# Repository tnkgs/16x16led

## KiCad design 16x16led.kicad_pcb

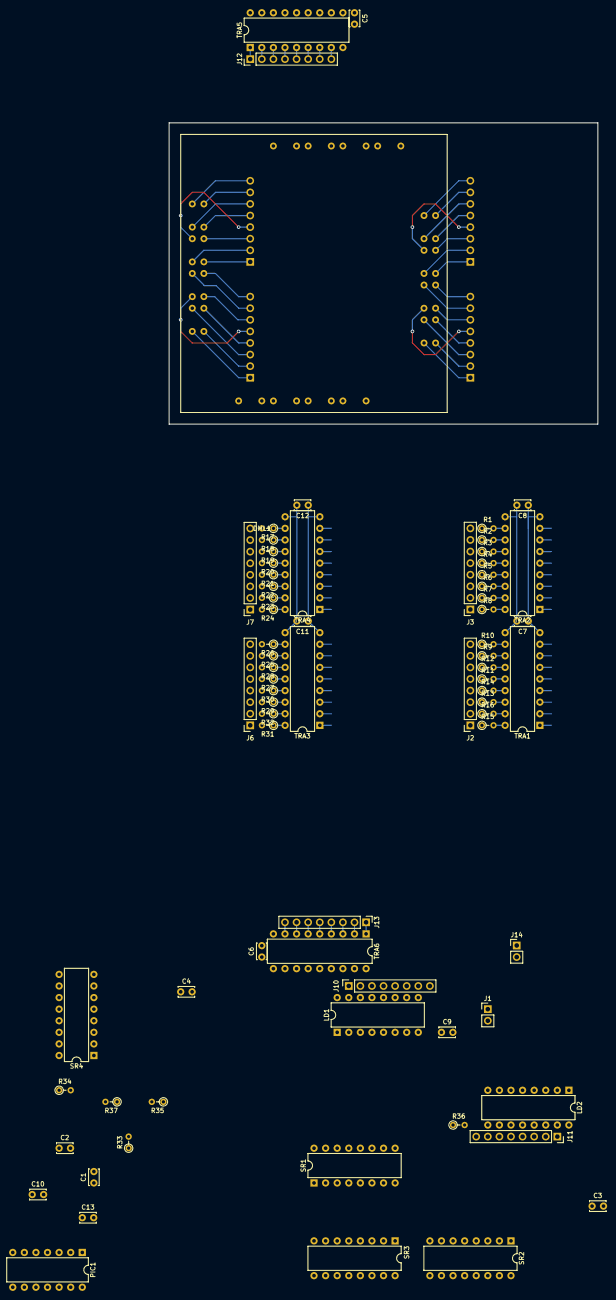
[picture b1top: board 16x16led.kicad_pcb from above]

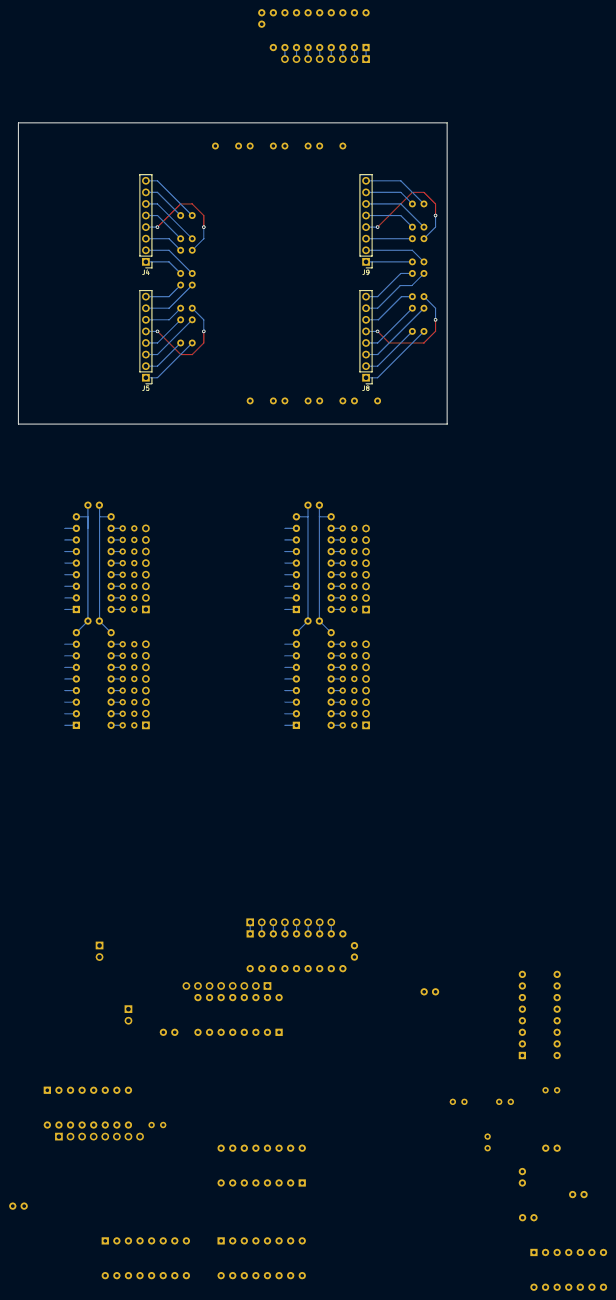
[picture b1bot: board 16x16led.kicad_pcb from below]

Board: 2 copper layers, 78 parts (4 on the bottom side), 165 nets.

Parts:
C1, C2, C3, C4, C5, C6, C7, C8, C9, C10, C11, C12, C13: 0.1; C_Disc_D3.4mm_W2.1mm_P2.50mm
DML1: LT-5016M1; LT-5016M1-Universal
J1, J14: Conn_01x02_Male; PinHeader_1x02_P2.54mm_Vertical
J2, J3, J6, J7, J10, J11: Conn_01x08_Female; PinSocket_1x08_P2.54mm_Vertical
J4, J5, J8, J9, J12, J13: Conn_01x08_Male; PinHeader_1x08_P2.54mm_Vertical
LD1, LD2: 74HC137; DIP-16_W7.62mm
PIC1: PIC16F1503-IP; DIP-14_W7.62mm
R1, R2, R3, R4, R5, R6, R7, R8, R9, R10, R11, R12, R13, R14, R15, R16, R17, R18, R19, R20, R21, R22, R23, R24, R25, R26, R27, R28, R29, R30, R31, R32: 330; R_Axial_DIN0204_L3.6mm_D1.6mm_P2.54mm_Vertical
R33, R34, R35, R36, R37: 10k; R_Axial_DIN0204_L3.6mm_D1.6mm_P2.54mm_Vertical
SR1, SR2, SR3, SR4: 74HC595; DIP-16_W7.62mm
TRA1, TRA2, TRA3, TRA4: TBD62083A; DIP-18_W7.62mm
TRA5, TRA6: TBD62783A; DIP-18_W7.62mm

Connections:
+5V: C1.2, C2.2, C3.2, C4.2, C9.2, C10.2, C13.2, LD1.16 (VCC), LD2.16 (VCC), PIC1.1 (VDD), R33.1, R34.1, R35.1, R36.1, R37.1, SR1.16 (VCC), SR2.16 (VCC), SR3.16 (VCC), SR4.16 (VCC)
/DA1: LD1.1 (A0), LD2.1 (A0), PIC1.10 (SCK/SCL/CLC2/C2IN+/AN4/RC0)
/DA2: LD1.2 (A1), LD2.2 (A1), PIC1.9 (SDI/SDA/PWM4/NCO1/C2IN1-/C1IN1-/AN5/RC1)
/DA3: LD1.3 (A2), LD2.3 (A2), PIC1.8 (SDO/C2IN2-/C1IN2-/AN6/RC2)
/DA4: LD1.5 (~E1), LD2.6 (E2), PIC1.7 (~SS/PWM2/CLCIN0/C2IN3-/C1IN3-/AN7/RC3)
/RCLK: PIC1.2 (RA5/T1CKI/NCO1CLK/CLCIN1/CLKIN), SR1.12 (RCLK), SR2.12 (RCLK), SR3.12 (RCLK), SR4.12 (RCLK)
/SA1: DML1.1 (Row1), TRA5.11 (O8)
/SA2: DML1.2 (Row2), TRA5.12 (O7)
/SA3: DML1.3 (Row3), TRA5.13 (O6)
/SA4: DML1.4 (Row4), TRA5.14 (O5)
/SA5: DML1.5 (Row5), TRA5.15 (O4)
/SA6: DML1.6 (Row6), TRA5.16 (O3)
/SA7: DML1.7 (Row7), TRA5.17 (O2)
/SA8: DML1.8 (Row8), TRA5.18 (O1)
/SA9: DML1.9 (Row9), TRA6.18 (O1)
/SA10: DML1.10 (Row10), TRA6.17 (O2)
/SA11: DML1.11 (Row11), TRA6.16 (O3)
/SA12: DML1.12 (Row12), TRA6.15 (O4)
/SA13: DML1.13 (Row13), TRA6.14 (O5)
/SA14: DML1.14 (Row14), TRA6.13 (O6)
/SA15: DML1.15 (Row15), TRA6.12 (O7)
/SA16: DML1.16 (Row16), TRA6.11 (O8)
/SC1: DML1.17 (Rd1), J8.2
/SC2: DML1.18 (Rd2), J8.1
/SC3: DML1.19 (Rd3), J8.4
/SC4: DML1.20 (Rd4), J8.3
/SC5: DML1.21 (Rd5), J8.6
/SC6: DML1.22 (Rd6), J8.5
/SC7: DML1.23 (Rd7), J8.8
/SC8: DML1.24 (Rd8), J8.7
/SC9: DML1.25 (Rd9), J9.1
/SC10: DML1.26 (Rd10), J9.2
/SC11: DML1.27 (Rd11), J9.3
/SC12: DML1.28 (Rd12), J9.4
/SC13: DML1.29 (Rd13), J9.5
/SC14: DML1.30 (Rd14), J9.6
/SC15: DML1.31 (Rd15), J9.7
/SC16: DML1.32 (Rd16), J9.8
/SER: PIC1.11 (RA2/AN2/DACOUT2/C1OUT/T0CKI/~CWG1FLT/CL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), SR1.14 (SER)
/SF1: DML1.33 (Gr1), J5.2
/SF2: DML1.34 (Gr2), J5.1
/SF3: DML1.35 (Gr3), J5.4
/SF4: DML1.36 (Gr4), J5.3
/SF5: DML1.37 (Gr5), J5.6
/SF6: DML1.38 (Gr6), J5.5
/SF7: DML1.39 (Gr7), J5.8
/SF8: DML1.40 (Gr8), J5.7
/SF9: DML1.41 (Gr9), J4.1
/SF10: DML1.42 (Gr10), J4.2
/SF11: DML1.43 (Gr11), J4.3
/SF12: DML1.44 (Gr12), J4.4
/SF13: DML1.45 (Gr13), J4.5
/SF14: DML1.46 (Gr14), J4.6
/SF15: DML1.47 (Gr15), J4.7
/SF16: DML1.48 (Gr16), J4.8
/SRCLK: PIC1.3 (RA4/AN3/T1G/NCO1/SDO/CLKOUT), SR1.11 (SRCLK), SR2.11 (SRCLK), SR3.11 (SRCLK), SR4.11 (SRCLK)
GND: C1.1, C2.1, C3.1, C4.1, C9.1, C10.1, C13.1, LD1.4 (~LE), LD1.8 (GND), LD2.4 (~LE), LD2.5 (~E1), LD2.8 (GND), PIC1.14 (VSS), SR1.8 (GND), SR1.13 (~OE), SR2.8 (GND), SR2.13 (~OE), SR3.8 (GND), SR3.13 (~OE), SR4.8 (GND), SR4.13 (~OE)
GND1: C5.1, C6.1, C7.1, C8.1, C11.1, C12.1, J14.2, TRA1.9 (GND), TRA2.9 (GND), TRA3.9 (GND), TRA4.9 (GND), TRA5.10 (GND), TRA6.10 (GND)
unnamed: J1.1, PIC1.5 (PWM1/CLC1/CWG1A/RC5)
unnamed: J1.2, PIC1.6 (CLC2IN1/CWG1B/C2OUT/RC4)
unnamed: J2.1, R15.1
unnamed: J2.2, R16.1
unnamed: J2.3, R13.1
unnamed: J2.4, R14.1
unnamed: J2.5, R11.1
unnamed: J3.1, R8.1
unnamed: J3.2, R7.1
unnamed: J3.3, R6.1
unnamed: J3.4, R5.1
unnamed: J3.5, R4.1
unnamed: J3.6, R3.1
unnamed: J3.7, R2.1
unnamed: J3.8, R1.1
unnamed: J6.1, R31.1
unnamed: J6.2, R32.1
unnamed: J7.8, R17.1
unnamed: J10.1, LD1.15 (~Y0)
unnamed: J10.2, LD1.14 (~Y1)
unnamed: J10.3, LD1.13 (~Y2)
unnamed: J10.4, LD1.12 (~Y3)
unnamed: J10.5, LD1.11 (~Y4)
unnamed: J10.6, LD1.10 (~Y5)
unnamed: J10.7, LD1.9 (~Y6)
unnamed: J10.8, LD1.7 (~Y7)
unnamed: J11.1, LD2.15 (~Y0)
unnamed: J11.2, LD2.14 (~Y1)
unnamed: J11.3, LD2.13 (~Y2)
unnamed: J11.4, LD2.12 (~Y3)
unnamed: J11.5, LD2.11 (~Y4)
unnamed: J11.6, LD2.10 (~Y5)
unnamed: J11.7, LD2.9 (~Y6)
unnamed: J11.8, LD2.7 (~Y7)
unnamed: J12.1, TRA5.1 (I1)
unnamed: J12.2, TRA5.2 (I2)
unnamed: J12.3, TRA5.3 (I3)
unnamed: J12.4, TRA5.4 (I4)
unnamed: J12.5, TRA5.5 (I5)
unnamed: J12.6, TRA5.6 (I6)
unnamed: J12.7, TRA5.7 (I7)
unnamed: J12.8, TRA5.8 (I8)
unnamed: J13.1, TRA6.1 (I1)
unnamed: J13.2, TRA6.2 (I2)
unnamed: J13.3, TRA6.3 (I3)
unnamed: J13.4, TRA6.4 (I4)
unnamed: J13.5, TRA6.5 (I5)
unnamed: J13.6, TRA6.6 (I6)
unnamed: J13.7, TRA6.7 (I7)
unnamed: J13.8, TRA6.8 (I8)
unnamed: LD1.6 (E2), R35.2
unnamed: R1.2, TRA2.11 (O8)
unnamed: R2.2, TRA2.12 (O7)
unnamed: R3.2, TRA2.13 (O6)
unnamed: R4.2, TRA2.14 (O5)
unnamed: J2.7, R9.1
unnamed: J2.8, R10.1
unnamed: J2.6, R12.1
unnamed: R17.2, TRA4.11 (O8)
unnamed: J7.7, R18.1
unnamed: R18.2, TRA4.12 (O7)
unnamed: J7.6, R19.1
unnamed: R19.2, TRA4.13 (O6)
unnamed: J7.5, R20.1
unnamed: R20.2, TRA4.14 (O5)
unnamed: J7.4, R21.1
unnamed: R21.2, TRA4.15 (O4)
unnamed: J7.3, R22.1
unnamed: R22.2, TRA4.16 (O3)
unnamed: J7.2, R23.1
unnamed: R23.2, TRA4.17 (O2)
unnamed: J7.1, R24.1
unnamed: R24.2, TRA4.18 (O1)
unnamed: J6.7, R25.1
unnamed: R25.2, TRA3.12 (O7)
unnamed: J6.8, R26.1
unnamed: R26.2, TRA3.11 (O8)
unnamed: J6.5, R27.1
unnamed: R27.2, TRA3.14 (O5)
unnamed: J6.6, R28.1
unnamed: R28.2, TRA3.13 (O6)
unnamed: J6.3, R29.1
unnamed: R29.2, TRA3.16 (O3)
unnamed: J6.4, R30.1
unnamed: R30.2, TRA3.15 (O4)
unnamed: R31.2, TRA3.18 (O1)
unnamed: R32.2, TRA3.17 (O2)
unnamed: R33.2, SR1.10 (~SRCLR)
unnamed: R34.2, SR2.10 (~SRCLR)
unnamed: R36.2, SR3.10 (~SRCLR)
unnamed: R37.2, SR4.10 (~SRCLR)
unnamed: SR1.9 (QH'), SR2.14 (SER)
unnamed: SR2.9 (QH'), SR3.14 (SER)
unnamed: SR3.9 (QH'), SR4.14 (SER)
unnamed: R10.2, TRA1.11 (O8)
unnamed: R9.2, TRA1.12 (O7)
unnamed: R12.2, TRA1.13 (O6)
unnamed: R11.2, TRA1.14 (O5)
unnamed: R14.2, TRA1.15 (O4)
unnamed: R13.2, TRA1.16 (O3)
unnamed: R16.2, TRA1.17 (O2)
unnamed: R15.2, TRA1.18 (O1)
unnamed: R5.2, TRA2.15 (O4)
unnamed: R6.2, TRA2.16 (O3)
unnamed: R7.2, TRA2.17 (O2)
unnamed: R8.2, TRA2.18 (O1)
VCC: C5.2, C6.2, C7.2, C8.2, C11.2, C12.2, J14.1, TRA1.10 (COM), TRA2.10 (COM), TRA3.10 (COM), TRA4.10 (COM), TRA5.9 (VCC), TRA6.9 (VCC)

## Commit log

2022-09-30 init
2022-09-30 readme
